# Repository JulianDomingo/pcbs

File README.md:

# pcbs
Public PCB files for my keyboard projects!

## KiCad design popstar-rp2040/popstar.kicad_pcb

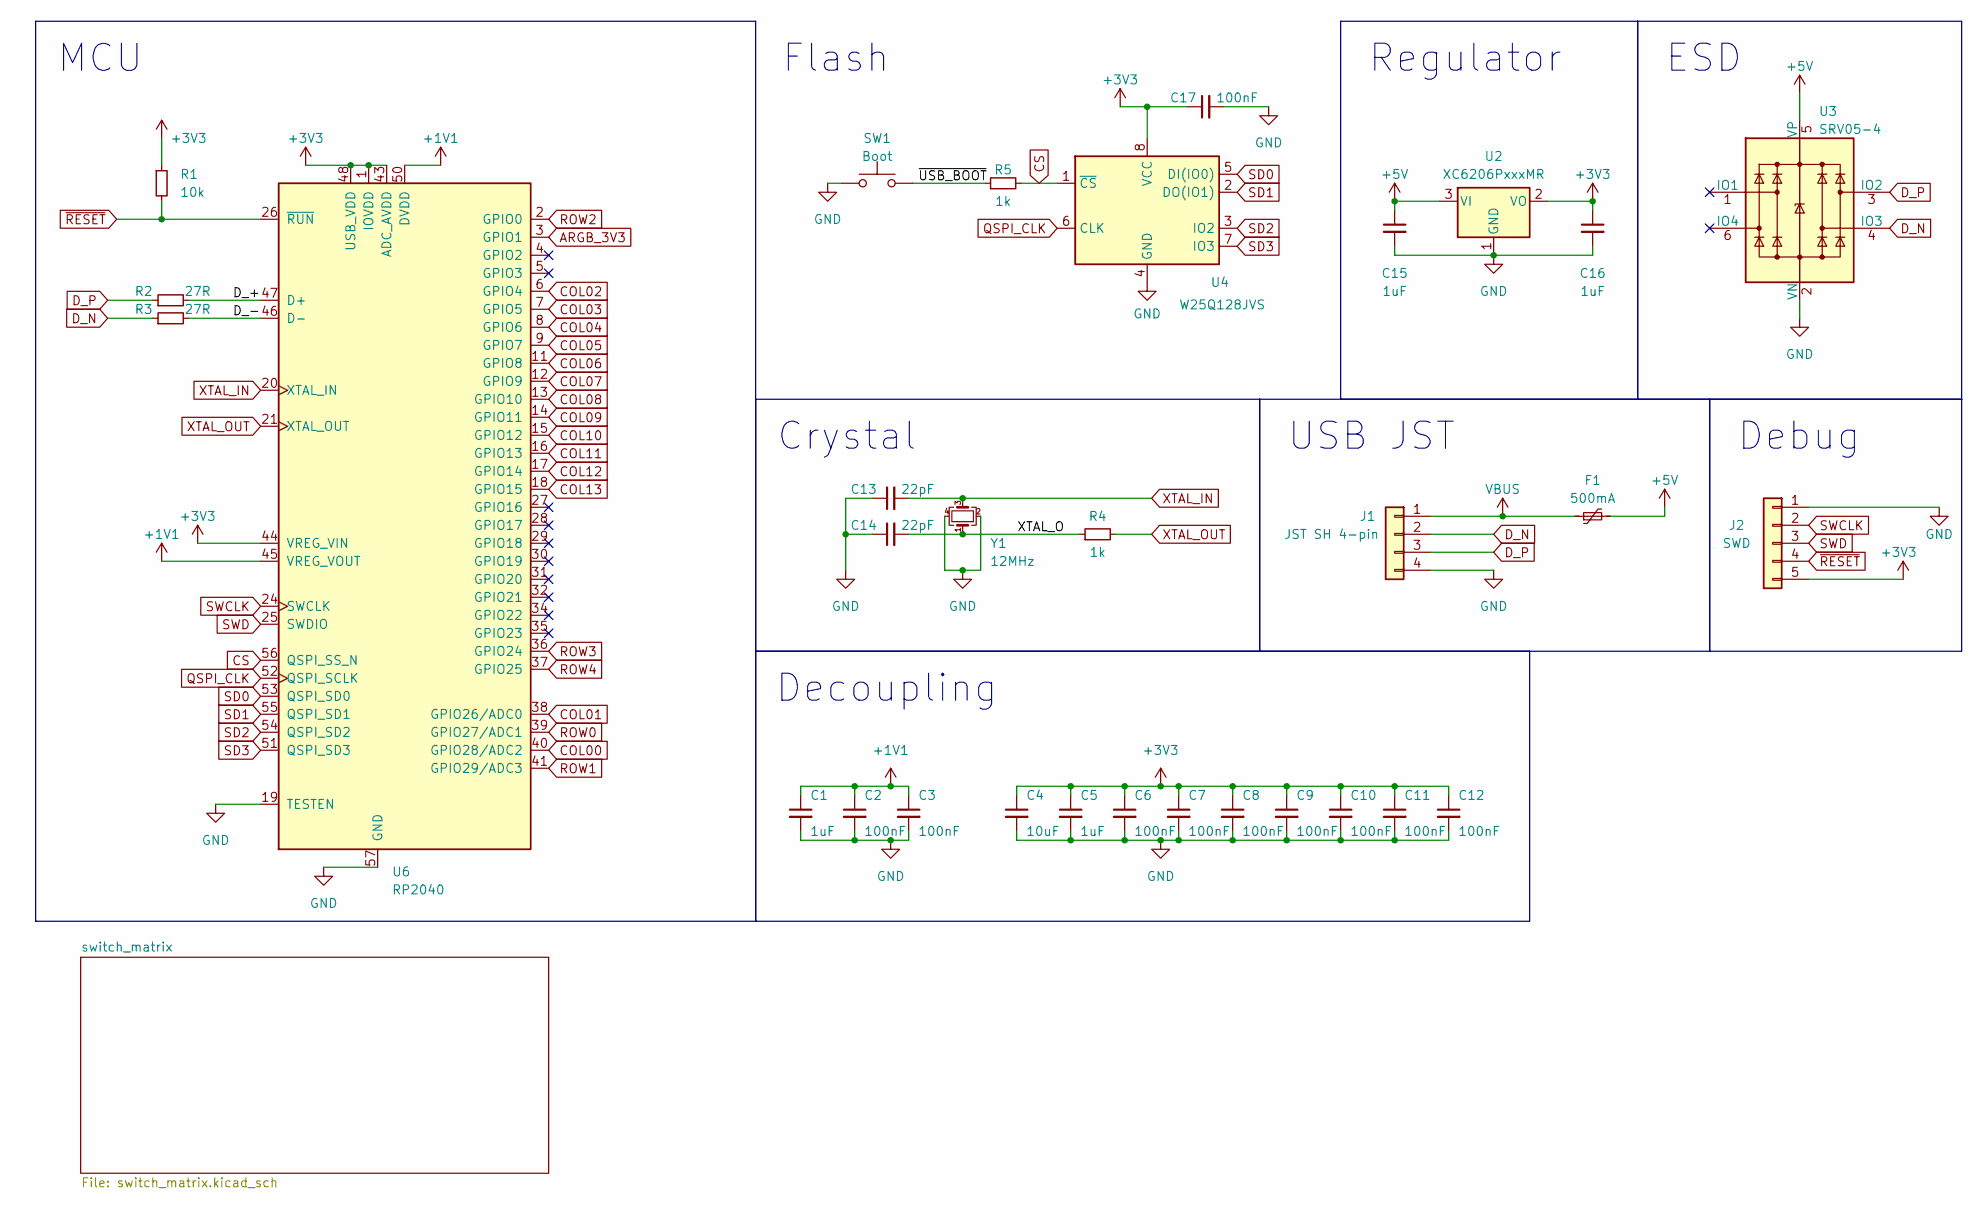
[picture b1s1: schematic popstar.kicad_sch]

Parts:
C1, C5, C15, C16: 1uF; C_0402_1005Metric; LCSC C52923
C2, C3, C6, C9, C10, C11, C12, C17: 100nF; C_0402_1005Metric; LCSC C1525
C4: 10uF; C_0402_1005Metric; LCSC C15525
C7, C8: 100nF; C_0402_1005Metric; LCSC 1525
C13, C14: 22pF; C_0402_1005Metric; LCSC C1555
F1: 500mA; Fuse_1206_3216Metric; LCSC C135342
J1: JST SH 4-pin; JST_SH_SM04B-SRSS-TB_1x04-1MP_P1.00mm_Horizontal; LCSC C160404
J2: SWD; PinSocket_1x05_P2.54mm_Vertical
R1: 10k; R_0402_1005Metric; LCSC C25744
R2, R3: 27R; R_0603_1608Metric; LCSC C25190
R4, R5: 1k; R_0402_1005Metric; LCSC C11702
SW1: Boot; PinSocket_1x02_P2.54mm_Vertical
U2: XC6206PxxxMR; SOT-23-3; LCSC C5446
U3: SRV05-4; SOT-23-6-routable; LCSC C85364
U4: W25Q128JVS; SOIC-8_5.23x5.23mm_P1.27mm; LCSC C97521
U6: RP2040; RP2040-QFN-56
Y1: 12MHz; Crystal_SMD_3225-4Pin_3.2x2.5mm; LCSC C9002

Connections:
+1V1: C1.1, C2.1, C3.1, U6.23 (DVDD), U6.45 (VREG_VOUT), U6.50 (DVDD)
+3V3: C4.1, C5.1, C6.1, C7.1, C8.1, C9.1, C10.1, C11.1, C12.1, C16.1, C17.1, J2.5, R1.1, U2.2 (VO), U4.8 (VCC), U6.1 (IOVDD), U6.10 (IOVDD), U6.22 (IOVDD), U6.33 (IOVDD), U6.42 (IOVDD), U6.43 (ADC_AVDD), U6.44 (VREG_VIN), U6.48 (USB_VDD), U6.49 (IOVDD)
+5V: C15.1, F1.2, U2.3 (VI), U3.5 (VP); also elsewhere on the board
/D_+: R2.2, U6.47 (D+)
/D_-: R3.2, U6.46 (D-)
/XTAL_O: C14.2, R4.1, Y1.1
/~USB_BOOT: R5.1, SW1.2
ARGB_3V3: U6.3 (GPIO1); also elsewhere on the board
COL00: U6.40 (GPIO28/ADC2); also elsewhere on the board
COL01: U6.38 (GPIO26/ADC0); also elsewhere on the board
COL02: U6.6 (GPIO4); also elsewhere on the board
COL03: U6.7 (GPIO5); also elsewhere on the board
COL04: U6.8 (GPIO6); also elsewhere on the board
COL05: U6.9 (GPIO7); also elsewhere on the board
COL06: U6.11 (GPIO8); also elsewhere on the board
COL07: U6.12 (GPIO9); also elsewhere on the board
COL08: U6.13 (GPIO10); also elsewhere on the board
COL09: U6.14 (GPIO11); also elsewhere on the board
COL10: U6.15 (GPIO12); also elsewhere on the board
COL11: U6.16 (GPIO13); also elsewhere on the board
COL12: U6.17 (GPIO14); also elsewhere on the board
COL13: U6.18 (GPIO15); also elsewhere on the board
CS: R5.2, U4.1 (~CS), U6.56 (QSPI_SS_N)
D_N: J1.2, R3.1, U3.4 (IO3)
D_P: J1.3, R2.1, U3.3 (IO2)
GND: C1.2, C2.2, C3.2, C4.2, C5.2, C6.2, C7.2, C8.2, C9.2, C10.2, C11.2, C12.2, C13.1, C14.1, C15.2, C16.2, C17.2, J1.4, J2.1, SW1.1, U2.1 (GND), U3.2 (VN), U4.4 (GND), U6.19 (TESTEN), U6.57 (GND), Y1.2, Y1.4; also elsewhere on the board
QSPI_CLK: U4.6 (CLK), U6.52 (QSPI_SCLK)
ROW0: U6.39 (GPIO27/ADC1); also elsewhere on the board
ROW1: U6.41 (GPIO29/ADC3); also elsewhere on the board
ROW2: U6.2 (GPIO0); also elsewhere on the board
ROW3: U6.36 (GPIO24); also elsewhere on the board
ROW4: U6.37 (GPIO25); also elsewhere on the board
SD0: U4.5 (DI(IO0)), U6.53 (QSPI_SD0)
SD1: U4.2 (DO(IO1)), U6.55 (QSPI_SD1)
SD2: U4.3 (IO2), U6.54 (QSPI_SD2)
SD3: U4.7 (IO3), U6.51 (QSPI_SD3)
SWCLK: J2.2, U6.24 (SWCLK)
SWD: J2.3, U6.25 (SWDIO)
VBUS: F1.1, J1.1
XTAL_IN: C13.2, U6.20 (XTAL_IN), Y1.3
XTAL_OUT: R4.2, U6.21 (XTAL_OUT)
~RESET: J2.4, R1.2, U6.26 (~RUN)

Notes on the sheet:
MCU
ESD
Regulator
Debug
Crystal
Flash
USB JST
Decoupling

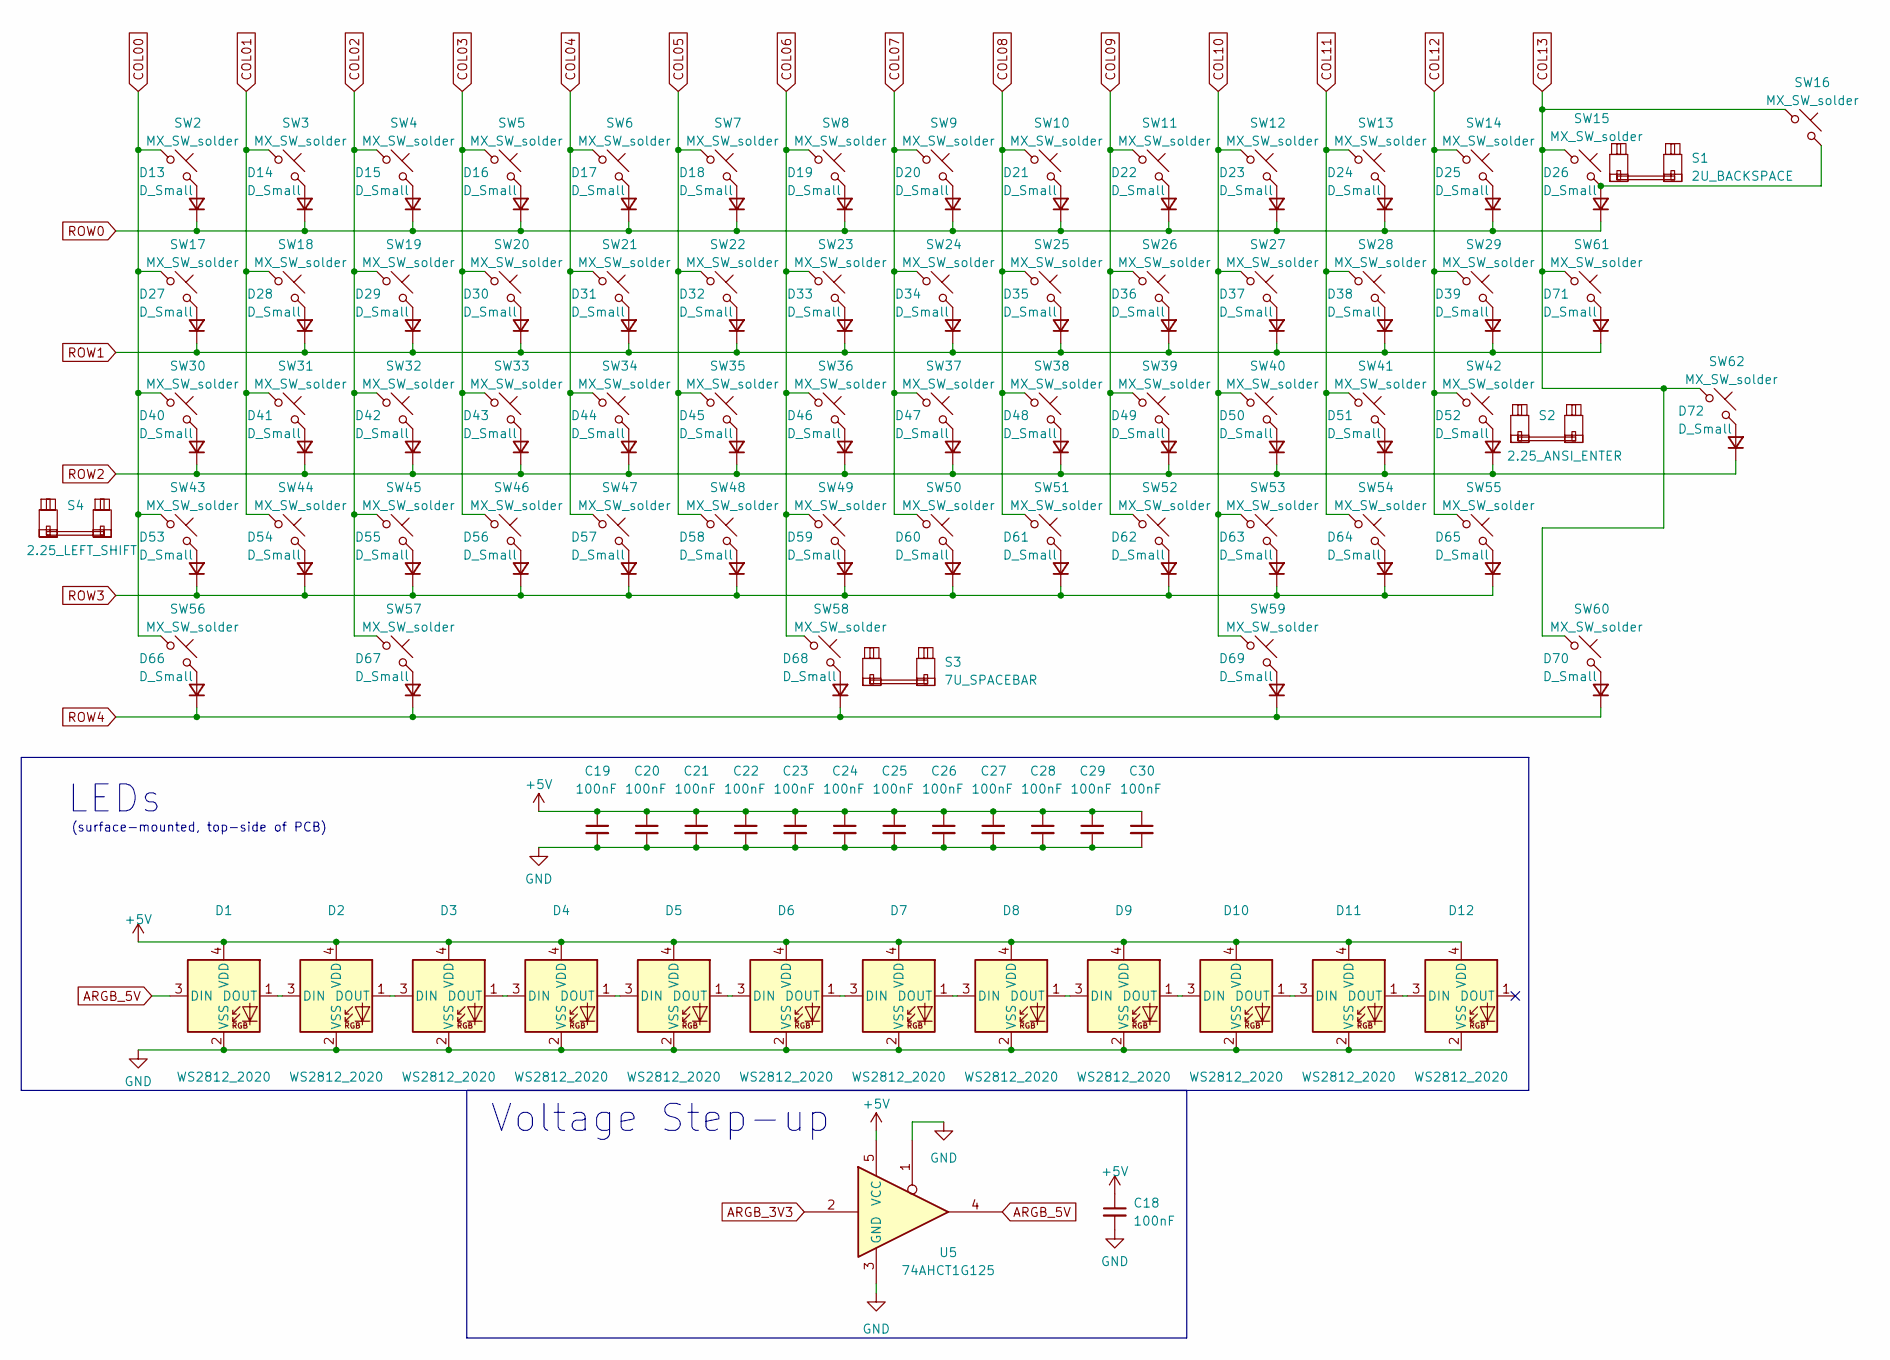
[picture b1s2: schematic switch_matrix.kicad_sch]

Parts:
C18, C19, C20, C21, C22, C23, C24, C25, C26, C27, C28, C29, C30: 100nF; C_0402_1005Metric; LCSC C1525
D1, D2, D3, D4, D5, D6, D7, D8, D9, D10, D11, D12: WS2812_2020; LED_WS2812_2020
D13, D14, D15, D16, D17, D18, D19, D20, D21, D22, D23, D24, D25, D26, D27, D28, D29, D30, D31, D32, D33, D34, D35, D36, D37, D38, D39, D40, D41, D42, D43, D44, D45, D46, D47, D48, D49, D50, D51, D52, D53, D54, D55, D56, D57, D58, D59, D60, D61, D62, D63, D64, D65, D66, D67, D68, D69, D70, D71, D72: D_Small; D_SOD-123; LCSC C81598
S1: 2U_BACKSPACE; STAB_MX_2u
S2: 2.25_ANSI_ENTER; STAB_MX_2.25u
S3: 7U_SPACEBAR; STAB_MX_P_7u
S4: 2.25_LEFT_SHIFT; STAB_MX_2.25u
SW2, SW3, SW4, SW5, SW6, SW7, SW8, SW9, SW10, SW11, SW12, SW13, SW14, SW15, SW16, SW18, SW19, SW20, SW21, SW22, SW23, SW24, SW25, SW26, SW27, SW28, SW29, SW31, SW32, SW33, SW34, SW35, SW36, SW37, SW38, SW39, SW40, SW41, SW42, SW43, SW44, SW45, SW46, SW47, SW48, SW49, SW50, SW51, SW52, SW53, SW55, SW58, SW61: MX_SW_solder; SW_MX_1u
SW17, SW56, SW57, SW59, SW60, SW62: MX_SW_solder; SW_MX_1.5u
SW30: MX_SW_solder; SW_MX_1.75u_stp
SW54: MX_SW_solder; SW_MX_1.75u
U5: 74AHCT1G125; SOT-23-5; LCSC C7484

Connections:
+5V: C18.1, C19.1, C20.1, C21.1, C22.1, C23.1, C24.1, C25.1, C26.1, C27.1, C28.1, C29.1, C30.1, D1.4 (VDD), D2.4 (VDD), D3.4 (VDD), D4.4 (VDD), D5.4 (VDD), D6.4 (VDD), D7.4 (VDD), D8.4 (VDD), D9.4 (VDD), D10.4 (VDD), D11.4 (VDD), D12.4 (VDD), U5.5 (VCC); also elsewhere on the board
ARGB_3V3: U5.2; also elsewhere on the board
ARGB_5V: D1.3 (DIN), U5.4
COL00: SW2.1, SW17.1, SW30.1, SW43.1, SW56.1; also elsewhere on the board
COL01: SW3.1, SW18.1, SW31.1, SW44.1; also elsewhere on the board
COL02: SW4.1, SW19.1, SW32.1, SW45.1, SW57.1; also elsewhere on the board
COL03: SW5.1, SW20.1, SW33.1, SW46.1; also elsewhere on the board
COL04: SW6.1, SW21.1, SW34.1, SW47.1; also elsewhere on the board
COL05: SW7.1, SW22.1, SW35.1, SW48.1; also elsewhere on the board
COL06: SW8.1, SW23.1, SW36.1, SW49.1, SW58.1; also elsewhere on the board
COL07: SW9.1, SW24.1, SW37.1, SW50.1; also elsewhere on the board
COL08: SW10.1, SW25.1, SW38.1, SW51.1; also elsewhere on the board
COL09: SW11.1, SW26.1, SW39.1, SW52.1; also elsewhere on the board
COL10: SW12.1, SW27.1, SW40.1, SW53.1, SW59.1; also elsewhere on the board
COL11: SW13.1, SW28.1, SW41.1, SW54.1; also elsewhere on the board
COL12: SW14.1, SW29.1, SW42.1, SW55.1; also elsewhere on the board
COL13: SW15.1, SW16.1, SW60.1, SW61.1, SW62.1; also elsewhere on the board
GND: C18.2, C19.2, C20.2, C21.2, C22.2, C23.2, C24.2, C25.2, C26.2, C27.2, C28.2, C29.2, C30.2, D1.2 (VSS), D2.2 (VSS), D3.2 (VSS), D4.2 (VSS), D5.2 (VSS), D6.2 (VSS), D7.2 (VSS), D8.2 (VSS), D9.2 (VSS), D10.2 (VSS), D11.2 (VSS), D12.2 (VSS), U5.1, U5.3 (GND); also elsewhere on the board
unnamed: D1.1 (DOUT), D2.3 (DIN)
unnamed: D2.1 (DOUT), D3.3 (DIN)
unnamed: D3.1 (DOUT), D4.3 (DIN)
unnamed: D4.1 (DOUT), D5.3 (DIN)
unnamed: D5.1 (DOUT), D6.3 (DIN)
unnamed: D6.1 (DOUT), D7.3 (DIN)
unnamed: D7.1 (DOUT), D8.3 (DIN)
unnamed: D8.1 (DOUT), D9.3 (DIN)
unnamed: D9.1 (DOUT), D10.3 (DIN)
unnamed: D10.1 (DOUT), D11.3 (DIN)
unnamed: D11.1 (DOUT), D12.3 (DIN)
unnamed: D13.2 (A), SW2.2
unnamed: D14.2 (A), SW3.2
unnamed: D15.2 (A), SW4.2
unnamed: D16.2 (A), SW5.2
unnamed: D17.2 (A), SW6.2
unnamed: D18.2 (A), SW7.2
unnamed: D19.2 (A), SW8.2
unnamed: D20.2 (A), SW9.2
unnamed: D21.2 (A), SW10.2
unnamed: D22.2 (A), SW11.2
unnamed: D23.2 (A), SW12.2
unnamed: D24.2 (A), SW13.2
unnamed: D25.2 (A), SW14.2
unnamed: D26.2 (A), SW15.2, SW16.2
unnamed: D27.2 (A), SW17.2
unnamed: D28.2 (A), SW18.2
unnamed: D29.2 (A), SW19.2
unnamed: D30.2 (A), SW20.2
unnamed: D31.2 (A), SW21.2
unnamed: D32.2 (A), SW22.2
unnamed: D33.2 (A), SW23.2
unnamed: D34.2 (A), SW24.2
unnamed: D35.2 (A), SW25.2
unnamed: D36.2 (A), SW26.2
unnamed: D37.2 (A), SW27.2
unnamed: D38.2 (A), SW28.2
unnamed: D39.2 (A), SW29.2
unnamed: D40.2 (A), SW30.2
unnamed: D41.2 (A), SW31.2
unnamed: D42.2 (A), SW32.2
unnamed: D43.2 (A), SW33.2
unnamed: D44.2 (A), SW34.2
unnamed: D45.2 (A), SW35.2
unnamed: D46.2 (A), SW36.2
unnamed: D47.2 (A), SW37.2
unnamed: D48.2 (A), SW38.2
unnamed: D49.2 (A), SW39.2
unnamed: D50.2 (A), SW40.2
unnamed: D51.2 (A), SW41.2
unnamed: D52.2 (A), SW42.2
unnamed: D53.2 (A), SW43.2
unnamed: D54.2 (A), SW44.2
unnamed: D55.2 (A), SW45.2
unnamed: D56.2 (A), SW46.2
unnamed: D57.2 (A), SW47.2
unnamed: D58.2 (A), SW48.2
unnamed: D59.2 (A), SW49.2
unnamed: D60.2 (A), SW50.2
unnamed: D61.2 (A), SW51.2
unnamed: D62.2 (A), SW52.2
unnamed: D63.2 (A), SW53.2
unnamed: D64.2 (A), SW54.2
unnamed: D65.2 (A), SW55.2
unnamed: D66.2 (A), SW56.2
unnamed: D67.2 (A), SW57.2
unnamed: D68.2 (A), SW58.2
unnamed: D69.2 (A), SW59.2
unnamed: D70.2 (A), SW60.2
unnamed: D71.2 (A), SW61.2
unnamed: D72.2 (A), SW62.2
ROW0: D13.1 (K), D14.1 (K), D15.1 (K), D16.1 (K), D17.1 (K), D18.1 (K), D19.1 (K), D20.1 (K), D21.1 (K), D22.1 (K), D23.1 (K), D24.1 (K), D25.1 (K), D26.1 (K); also elsewhere on the board
ROW1: D27.1 (K), D28.1 (K), D29.1 (K), D30.1 (K), D31.1 (K), D32.1 (K), D33.1 (K), D34.1 (K), D35.1 (K), D36.1 (K), D37.1 (K), D38.1 (K), D39.1 (K), D71.1 (K); also elsewhere on the board
ROW2: D40.1 (K), D41.1 (K), D42.1 (K), D43.1 (K), D44.1 (K), D45.1 (K), D46.1 (K), D47.1 (K), D48.1 (K), D49.1 (K), D50.1 (K), D51.1 (K), D52.1 (K), D72.1 (K); also elsewhere on the board
ROW3: D53.1 (K), D54.1 (K), D55.1 (K), D56.1 (K), D57.1 (K), D58.1 (K), D59.1 (K), D60.1 (K), D61.1 (K), D62.1 (K), D63.1 (K), D64.1 (K), D65.1 (K); also elsewhere on the board
ROW4: D66.1 (K), D67.1 (K), D68.1 (K), D69.1 (K), D70.1 (K); also elsewhere on the board

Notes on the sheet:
(surface-mounted, top-side of PCB)
LEDs
Voltage Step-up

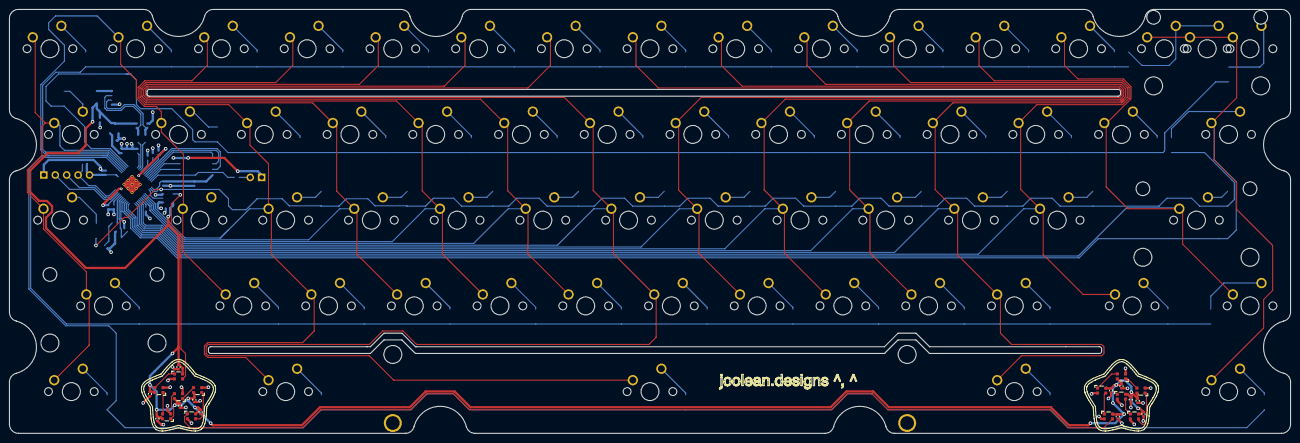
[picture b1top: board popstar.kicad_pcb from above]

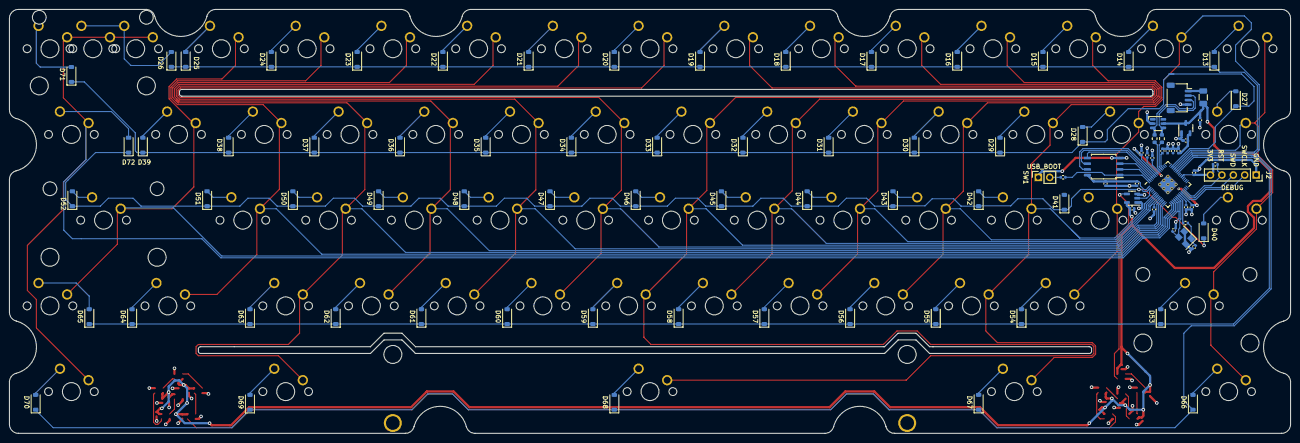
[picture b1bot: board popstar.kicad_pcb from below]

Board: 2 copper layers, 284.7 x 94.2 mm, 182 parts (93 on the bottom side), 114 nets.

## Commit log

2023-02-25 Add popstar dir, submodules for MX footprints + usb connectors
2023-02-25 Added footprint libraries, updated dir structure
2023-02-26 Added KLE for popstar + gitignore file
2023-02-26 Added outline for switch footprints / dimensions + KLE json
2023-02-26 Added planned traces for schematic
2023-02-26 Added marbastlib submodule
2023-02-26 Updated .gitignore
2023-02-26 Rearranged directories
2023-02-26 Added RP2040 version of popstar (branched from ice60)
2023-02-26 Repurposed 'popstar' to be ai03 tutorial. Real popstar PCB design will be in rp2040 folder.
2023-02-26 Added notes on decoupling capacitors, small progress on ai03 guide
2023-02-26 Updated decoupling caps notes
2023-02-26 Renamed popstar-rp2040 => reference rp2040. Created an actual dir for popstar rp2040 design.
2023-02-27 Added circuitry schematics for RP2040 popstar, excluding switch matrix and LEDs
2023-03-05 Added surface-mounted LEDs for shinethrough on WKL blockers.
2023-03-05 Cleaned up LED schematic impl.
2023-03-06 Added BOM spreadsheet, updated components with LCSC part numbers and footprints.
2023-03-06 Finished switch matrix, updated pin connections accordingly
2023-03-07 Fixed missing footprints in schematic, added barfed out components in PCB editor. Properly connected sleep-lib symbol libraries into popstar project.
2023-03-08 Correct 2.25 left shift to use 2.25 stab footprint
2023-03-09 Placed switch, stabs, and diode components in the proper places.
2023-03-09 Placed crystal oscillator components in the proper places.
2023-03-10 Added edge cuts, front silkscreen, adjusted diodes to not interfere with edge cuts
2023-03-10 Removed silkscreen near MCU + silkscreen collision with star LEDs
2023-03-10 Added more decoupling capacitors near MCU, debug, cleaned up component positioning a bit
2023-03-10 Removed F.Cu + 3D connector for debug/boot, corrected through-holes for 7u stab
2023-03-11 Finished placing all components within the courtyard.
2023-03-11 Added default trace widths, added routing for some of the decoupling caps
2023-03-11 Tweaked JST position to align fully with H60
2023-03-11 Routed debug
2023-03-12 Routed crystal oscillator, changed up GPIO pins for cleaner switch matrix routing
2023-03-12 Fixed routing issue on one of the decoupling caps, increased traces from MCU to 0.20mm
2023-03-12 Routed JST connector, ESD, voltage regulator, and more decoupling caps.
2023-03-12 Routed remainder of decoupling caps.
2023-03-12 Routed flash, boot
2023-03-12 Properly connected diodes to switches in the schematic
2023-03-12 Finished routing rows, cleaned up existing traces. Switched row0 and col0 for cleaner routing.
2023-03-12 Further removed some duplicate, unconnected traces
2023-03-12 Updated notes
2023-03-12 Fixed all DRC errors unrelated to split BS
2023-03-12 Updated traces near voltage step up component
2023-03-12 Repositioned row 2 diodes for proper routing of switch matrix columns
2023-03-13 Fixed footprint mismatch for stabs
2023-03-13 Fixed remainder of mismatched footprints. Simply did 'Change Footprint', but used the same name.
2023-03-13 Fixed more DRC errors, routed columns, added front Cu on GND pins for MCU
2023-03-13 Finished routing columns for rows 2, 3, 4
2023-03-13 Finshed routing columns for row 5
2023-03-13 Finished routing columns for row 1
2023-03-13 Changed column trace to front for right ctrl
2023-03-13 Removed f.mask from debug and boot + extraneous kicad components
2023-03-13 Reinstated f.mask and extraneous components for flash and boot to suppress DRC warnings. Fixed remainder of trace DRC errors.
2023-03-13 Started out routing for step up voltage
2023-03-13 Repositioned star LEDs for more convenient routing, WIP
2023-03-16 Finished up routing for left star blocker, moved one of the 3V3 decoupling capacitors closer to MCU
2023-03-16 Routed right star blocker, fixed non-GND VIA DRC warnings
2023-03-18 Added F.Cu and B.Cu ground fills, cleaned p DRC violations
2023-03-19 Cleaned up GND stitching for 5V
2023-03-19 Fixed all DRC errors, added copper zones for 1V1 and 3V3
2023-03-19 Cleaned up GND via stitching again
2023-03-19 Added back silkscreen for key indicators, additinoal GND stitching vias for assurance
2023-03-19 Added LCSC part for LEDs, gerber files for prod
2023-03-19 Updated LEDs to use SK6812MINI-E (rev mount) in schematic. PCB design update WIP.
2023-03-19 Finished re-design for left blocker LEDs
2023-03-19 Finished routing to the right LED blocker
2023-03-20 Removed star F.Silkscreen to remove DRC warnings, cleaned up rest of DRC violations from new LED routing
2023-03-20 Updated production files
2023-03-20 Updated STEP file
2023-03-20 Used unedit footprints for LEDs
2023-03-20 Attempting to get rid of annoying resurfacing DRC warnings related to footprints
2023-05-06 First v2 pcb commit, updated edge cut dimensions and rerouted traces to accommodate it.
2023-05-06 Changed primary JST location to center of PCB (between U and Y key), rerouted traces accordingly.
2023-05-07 Fixed unconnected trace ends, updated f.silkscreen
2023-06-08 oh god I haven't committed in over 3 months
